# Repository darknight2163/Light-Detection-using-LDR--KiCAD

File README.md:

# Light-Detection-using-LDR--KiCAD
PCB of Darkness Detector project implemented using LDR and transistor BC547. I have attached BOM, documents, schematics view, 3D design of PCB, and python code from Ki-CAD software in the zipped submitted file.

# Introduction
A circuit that detects darkness or a lack of light is known as a darkness detector or dark detector. In this
project, we've used the LDR, the most basic of all light sensors, to construct a straightforward darkness
detector circuit (Light Dependent Resistor). These darkness detector circuits can be utilised in systems
that switch on lights automatically when it becomes dark. Some parts are passive, such as capacitors and
resistors. LED has been used as an alarm to signal nighttime. This straightforward project's goal is to use
an LDR to detect darkness and an LED to illuminate it.
# Circuit Diagram of Darkness Detector
The following image shows the simple circuit diagram for the Darkness Detector project implemented
using LDR and transistor BC547:

# Working
1. In this project, a straightforward darkness detector is created. Transistor and LDR are two
extremely basic components used in the project's implementation (a few passive components as
well). Here, the project's operation is discussed.
2. The LDR's resistance decreases dramatically in the presence of sufficient light. Under these
circumstances, the voltage divider created by the LDR and 1 k resistor will output almost 0V. You
won't see any output at the transistor's output pin as a consequence.
3. The amount of light shining on the LDR will be reduced if we obstruct it with a hand or other
object. The LDR's resistance will rise as resistance does. The light detection will work since an
LED was attached to the transistor IC's output pin. As a result, the LED will be off while there is
sufficient light on the LDR, and it will turn on and shine when it is dark.
# Advantages
1. It is a very straightforward darkness detector with extremely minimal hardware and circuitry.
2. This project may be implemented without the need of any complicated microcontroller circuitry
or programming.
# Disadvantages
1. The system is transistor-controlled; therefore, the outcomes might not be as precise as
anticipated.
# Applications
1. This project may be used in systems that turn on lights automatically when it becomes dark.
2. This circuit may be a component of a larger system or undertaking, such as a home automation or
security system.

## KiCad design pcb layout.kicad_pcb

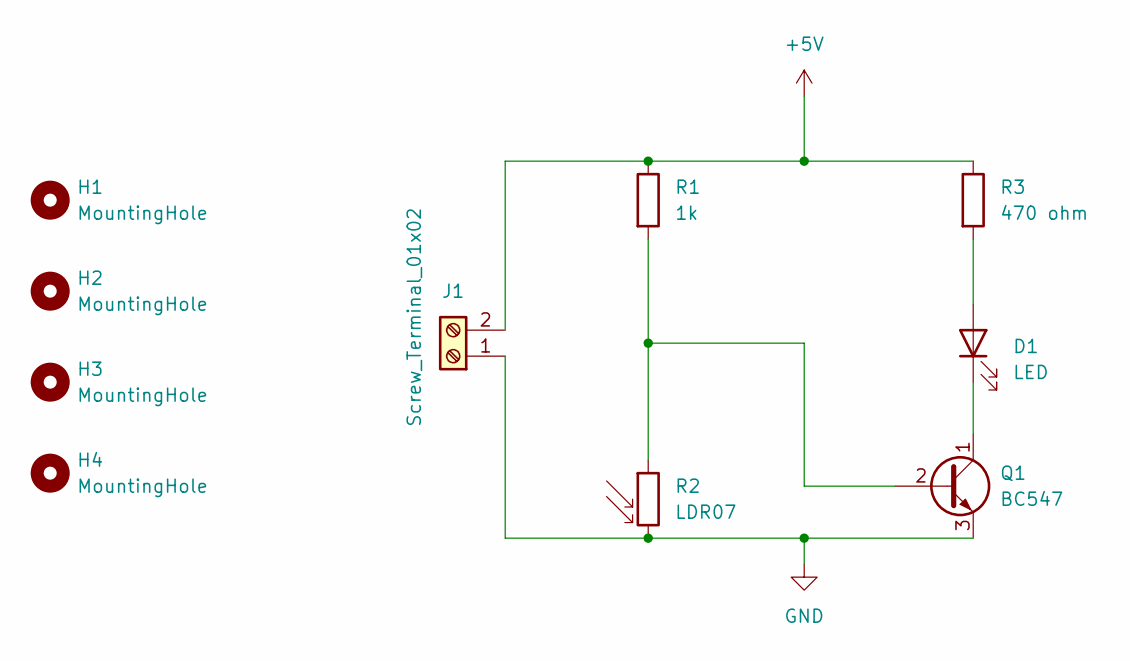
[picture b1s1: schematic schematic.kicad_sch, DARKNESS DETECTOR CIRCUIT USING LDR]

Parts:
D1: LED; LED_D3.0mm
H1, H2, H3, H4: MountingHole; MountingHole_2.2mm_M2_Pad_Via
J1: Screw_Terminal_01x02; TerminalBlock_bornier-2_P5.08mm
Q1: BC547; TO-92_Inline
R1: 1k; R_Axial_DIN0309_L9.0mm_D3.2mm_P12.70mm_Horizontal
R2: LDR07; R_LDR_5.1x4.3mm_P3.4mm_Vertical
R3: 470 ohm; R_Axial_DIN0309_L9.0mm_D3.2mm_P12.70mm_Horizontal

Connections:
+5V: J1.2, R1.1, R3.1
GND: J1.1, Q1.3 (E), R2.2
unnamed: D1.1 (K), Q1.1 (C)
unnamed: D1.2 (A), R3.2
unnamed: Q1.2 (B), R1.2, R2.1

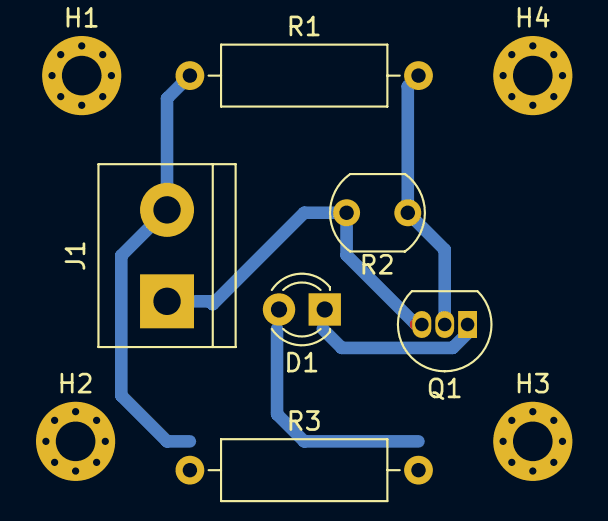
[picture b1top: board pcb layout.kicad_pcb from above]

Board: 2 copper layers, 10 parts (0 on the bottom side), 5 nets.

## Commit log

2023-12-08 Rename 5th PCB Design Contest.pdf to readme.md
2023-12-08 Rename README.md to r
2023-12-08 Rename readme.md to README.md
